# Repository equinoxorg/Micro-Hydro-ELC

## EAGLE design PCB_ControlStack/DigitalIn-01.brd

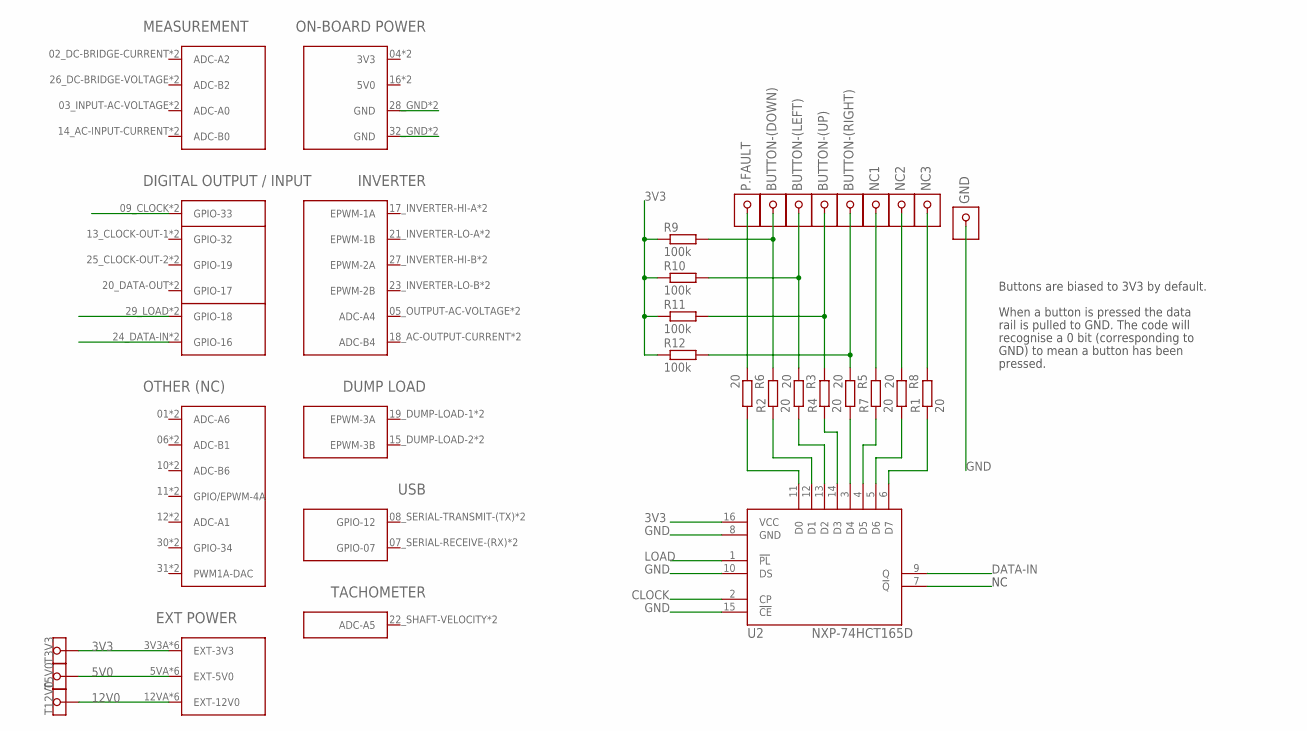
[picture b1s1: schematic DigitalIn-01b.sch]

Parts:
BUTTON-(DOWN): 1X1HEADER(W/VIA)
BUTTON-(LEFT): 1X1HEADER(W/VIA)
BUTTON-(RIGHT): 1X1HEADER(W/VIA)
BUTTON-(UP): 1X1HEADER(W/VIA)
GND: 1X1HEADER(W/VIA)
NC1, NC2, NC3: 1X1HEADER(W/VIA)
P.FAULT: 1X1HEADER(W/VIA)
R1, R2, R3, R4, R5, R6, R7, R8: 20; R0805
R9, R10, R11, R12: 100k; R0805
T3V3, T5V0, T12V0: TESTPAD
U1: CONTROLLER_STACK
U2: NXP-74HCT165D; SOIC-16D

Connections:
3V3: R9.1, R10.1, R11.1, R12.1, T3V3.TP, U1.3V3A (EXT-3V3), U1.3V3B (EXT-3V3), U1.3V3C (EXT-3V3), U1.3V3D (EXT-3V3), U1.3V3E (EXT-3V3), U1.3V3F (EXT-3V3), U2.16 (VCC)
5V0: T5V0.TP, U1.5VA (EXT-5V0), U1.5VB (EXT-5V0), U1.5VC (EXT-5V0), U1.5VD (EXT-5V0), U1.5VE (EXT-5V0), U1.5VF (EXT-5V0)
12V0: T12V0.TP, U1.12VA (EXT-12V0), U1.12VB (EXT-12V0), U1.12VC (EXT-12V0), U1.12VD (EXT-12V0), U1.12VE (EXT-12V0), U1.12VF (EXT-12V0)
CLOCK: U1.09_CLOCK (GPIO-33), U1.C9 (GPIO-33), U2.2 (CP)
DATA-IN: U1.24_DATA-IN (GPIO-16), U1.C24 (GPIO-16), U2.9 (Q)
GND: GND.P$2, GND.P$3, GND.P$4, GND.PAD, U1.28_GND (GND), U1.32_GND (GND), U1.C28 (GND), U1.C32 (GND), U2.8 (GND), U2.10 (DS), U2.15 (!CE)
LOAD: U1.29_LOAD (GPIO-18), U1.C29 (GPIO-18), U2.1 (!PL)
unnamed: R6.2, U2.11 (D0)
unnamed: R2.1, U2.12 (D1)
unnamed: R3.2, U2.13 (D2)
unnamed: R4.1, U2.14 (D3)
unnamed: P.FAULT.P$2, P.FAULT.P$3, P.FAULT.P$4, P.FAULT.PAD, R6.1
unnamed: R7.1, U2.4 (D5)
unnamed: R8.2, U2.5 (D6)
unnamed: R1.1, U2.6 (D7)
unnamed: R5.2, U2.3 (D4)
unnamed: BUTTON-(DOWN).P$2, BUTTON-(DOWN).P$3, BUTTON-(DOWN).P$4, BUTTON-(DOWN).PAD, R2.2, R9.2
unnamed: BUTTON-(LEFT).P$2, BUTTON-(LEFT).P$3, BUTTON-(LEFT).P$4, BUTTON-(LEFT).PAD, R3.1, R10.2
unnamed: BUTTON-(UP).P$2, BUTTON-(UP).P$3, BUTTON-(UP).P$4, BUTTON-(UP).PAD, R4.2, R11.2
unnamed: BUTTON-(RIGHT).P$2, BUTTON-(RIGHT).P$3, BUTTON-(RIGHT).P$4, BUTTON-(RIGHT).PAD, R5.1, R12.2
unnamed: NC1.P$2, NC1.P$3, NC1.P$4, NC1.PAD, R7.2
unnamed: NC2.P$2, NC2.P$3, NC2.P$4, NC2.PAD, R8.1
unnamed: NC3.P$2, NC3.P$3, NC3.P$4, NC3.PAD, R1.2

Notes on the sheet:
Buttons are biased to 3V3 by default.
When a button is pressed the data
rail is pulled to GND. The code will
recognise a 0 bit (corresponding to
GND) to mean a button has been
pressed.

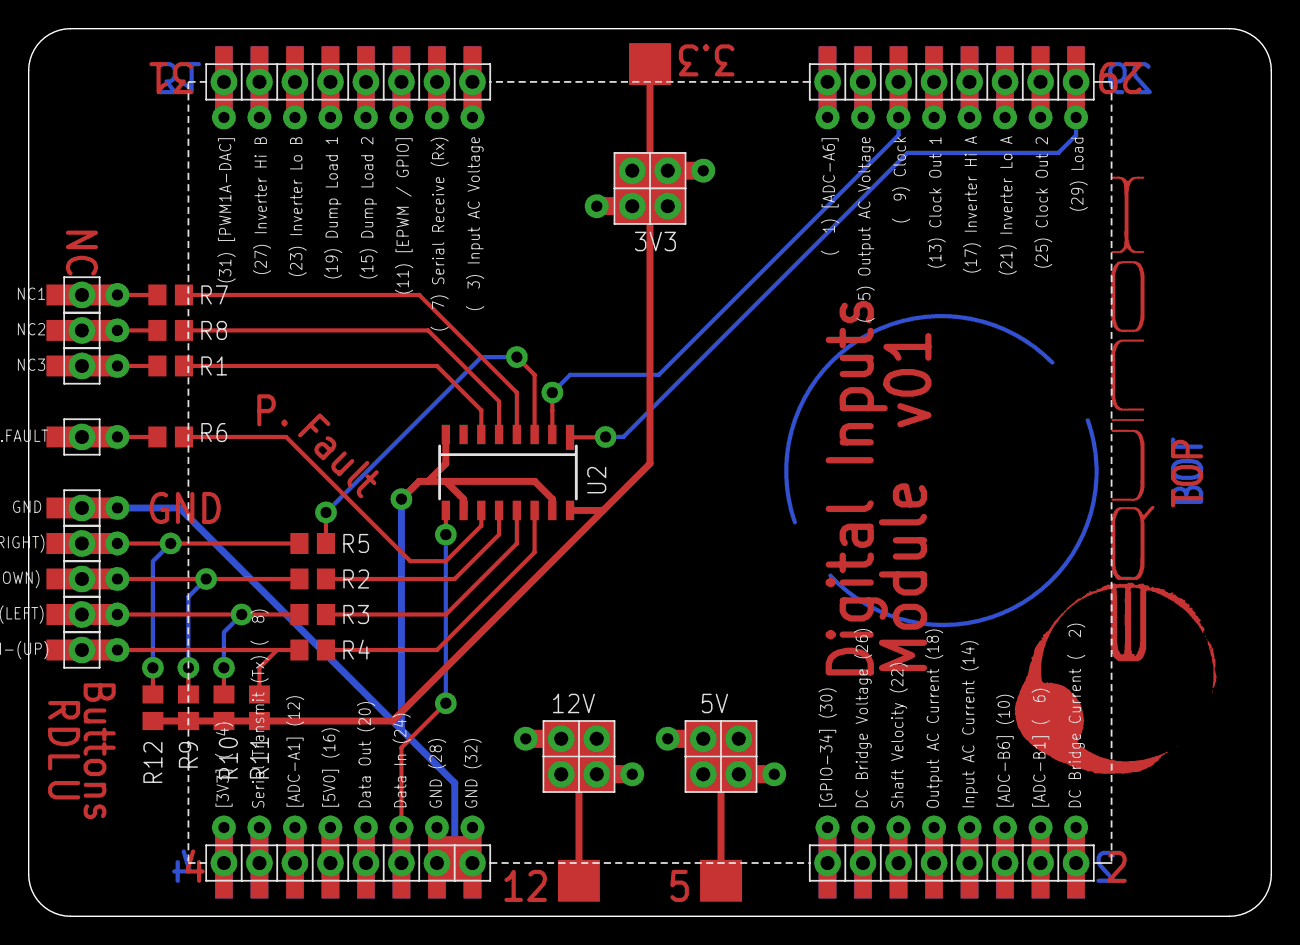
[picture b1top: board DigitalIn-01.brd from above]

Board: 2 copper layers, 88.9 x 63.5 mm, 26 parts (0 on the bottom side), 23 nets.

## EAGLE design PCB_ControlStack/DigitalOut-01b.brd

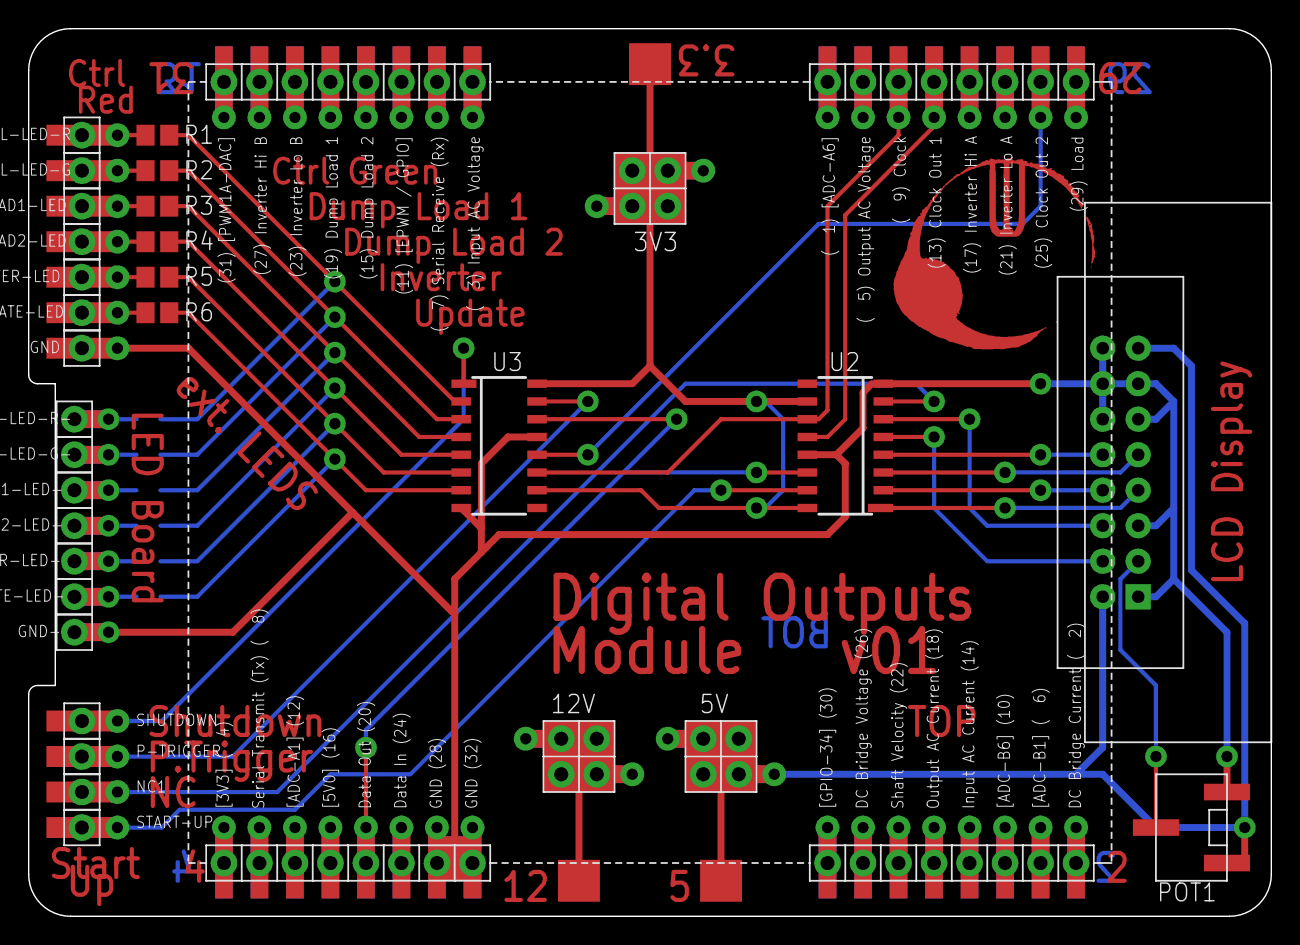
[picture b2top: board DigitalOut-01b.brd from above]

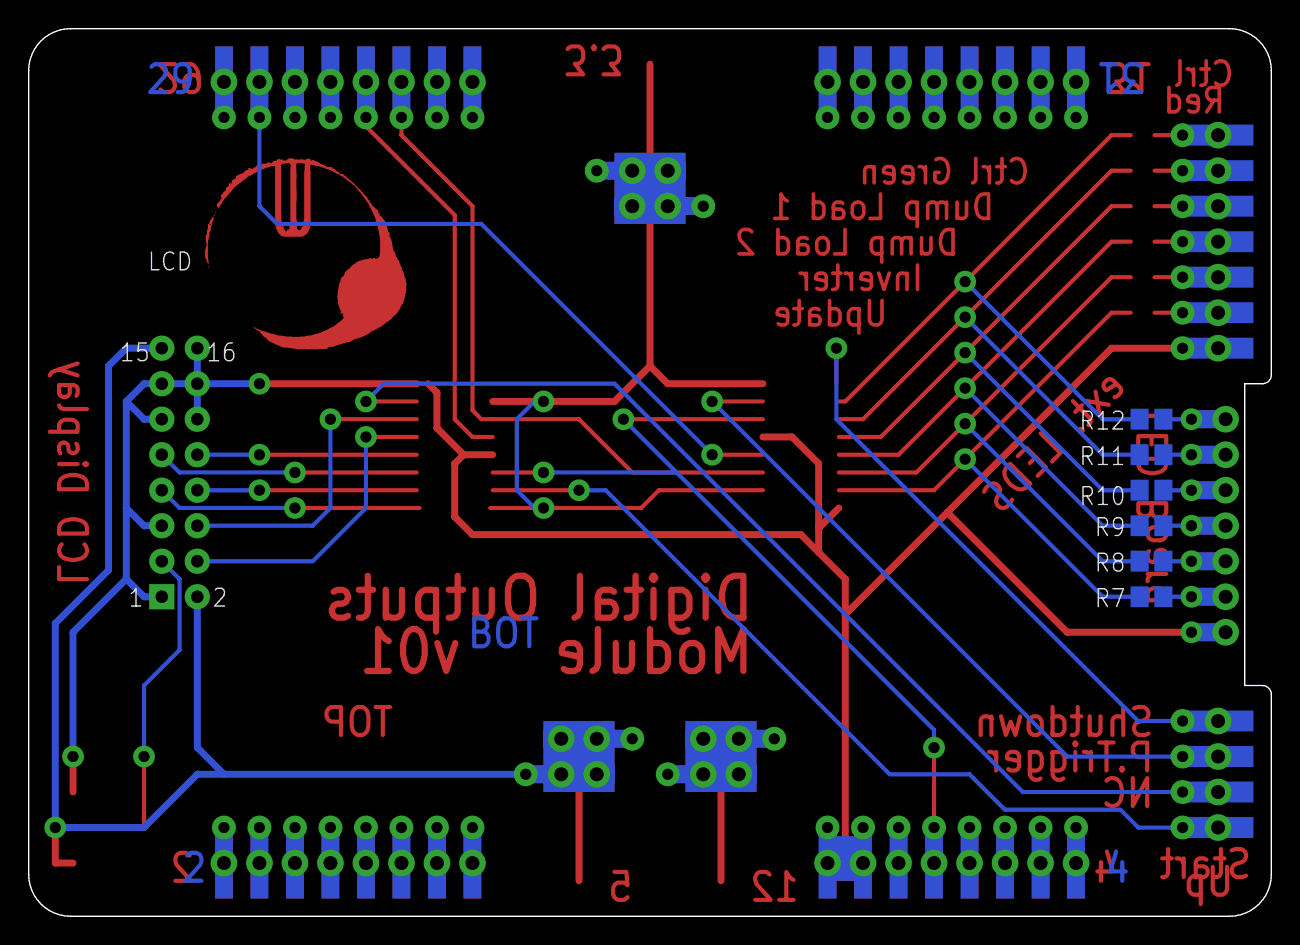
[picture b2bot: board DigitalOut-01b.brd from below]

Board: 2 copper layers, 88.9 x 63.5 mm, 38 parts (6 on the bottom side), 37 nets.

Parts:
CTRL-LED-G: 1X1HEADER(W/VIA)
CTRL-LED-G-: 1X1HEADER
CTRL-LED-R: 1X1HEADER(W/VIA)
CTRL-LED-R-: 1X1HEADER
DUMPLOAD1-LED, DUMPLOAD2-LED: 1X1HEADER(W/VIA)
DUMPLOAD1-LED-, DUMPLOAD2-LED-: 1X1HEADER
GND: 1X1HEADER(W/VIA)
GND-: 1X1HEADER
INVERTER-LED: 1X1HEADER(W/VIA)
INVERTER-LED-: 1X1HEADER
NC1: 1X1HEADER(W/VIA)
P-TRIGGER: 1X1HEADER(W/VIA)
POT1: BOURNS-3361S
R1, R2, R3, R4, R5, R6, R7, R8, R9, R10, R11, R12: 150; R0805
SHUTDOWN: 1X1HEADER(W/VIA)
START-UP: 1X1HEADER(W/VIA)
T3V3, T5V0, T12V0: TESTPAD
U1: CONTROLLER_STACK
U2, U3: TI-SN74AHC595D; SOIC-16D
U4: MULTICOMP-MC9B232
UPDATE-LED: 1X1HEADER(W/VIA)
UPDATE-LED-: 1X1HEADER

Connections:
3V3: T3V3.TP, U1.3V3A, U1.3V3B, U1.3V3C, U1.3V3D, U1.3V3E, U1.3V3F, U2.10, U2.16, U3.10, U3.16
5V0: POT1.2, T5V0.TP, U1.5VA, U1.5VB, U1.5VC, U1.5VD, U1.5VE, U1.5VF, U4.2, U4.15
12V0: T12V0.TP, U1.12VA, U1.12VB, U1.12VC, U1.12VD, U1.12VE, U1.12VF
CLOCK: U1.09_CLOCK, U1.C9, U2.11, U3.11
CLOCK-OUT-1: U1.13_CLOCK-OUT-1, U1.C13, U2.12
CLOCK-OUT-2: U1.25_CLOCK-OUT-2, U1.C25, U3.12
CONTRAST: POT1.3, U4.3
CTRL-LED-1: R1.1, R12.1, U3.2
CTRL-LED-2: R2.2, R11.2, U3.3
DATA-OUT: U1.20_DATA-OUT, U1.C20, U2.14, U3.14
DB0: U2.1, U4.7
DB1: U2.2, U4.8
DB2: U2.3, U4.9
DB3: U2.4, U4.10
DUMPLOAD1-LED: R3.1, R10.1, U3.4
DUMPLOAD2-LED: R4.2, R9.2, U3.5
ENABLE: U2.6, U4.6
GND: GND.P$2, GND.P$3, GND.P$4, GND.PAD, GND-.P$1, POT1.1, U1.28_GND, U1.32_GND, U1.C28, U1.C32, U2.8, U2.13, U3.8, U3.13, U4.1, U4.5, U4.11, U4.12, U4.13, U4.14, U4.16
INVERTER-LED: R5.1, R8.1, U3.6
unnamed: R7.1, UPDATE-LED-.P$1
unnamed: INVERTER-LED-.P$1, R8.2
unnamed: DUMPLOAD2-LED-.P$1, R9.1
unnamed: DUMPLOAD1-LED-.P$1, R10.2
unnamed: CTRL-LED-G-.P$1, R11.1
unnamed: CTRL-LED-R.P$2, CTRL-LED-R.P$3, CTRL-LED-R.P$4, CTRL-LED-R.PAD, R1.2
unnamed: CTRL-LED-R-.P$1, R12.2
unnamed: CTRL-LED-G.P$2, CTRL-LED-G.P$3, CTRL-LED-G.P$4, CTRL-LED-G.PAD, R2.1
unnamed: DUMPLOAD1-LED.P$2, DUMPLOAD1-LED.P$3, DUMPLOAD1-LED.P$4, DUMPLOAD1-LED.PAD, R3.2
unnamed: DUMPLOAD2-LED.P$2, DUMPLOAD2-LED.P$3, DUMPLOAD2-LED.P$4, DUMPLOAD2-LED.PAD, R4.1
unnamed: NC1.P$2, NC1.P$3, NC1.P$4, NC1.PAD, U2.7
unnamed: INVERTER-LED.P$2, INVERTER-LED.P$3, INVERTER-LED.P$4, INVERTER-LED.PAD, R5.2
unnamed: R6.1, UPDATE-LED.P$2, UPDATE-LED.P$3, UPDATE-LED.P$4, UPDATE-LED.PAD
P-TRIGGER: P-TRIGGER.P$2, P-TRIGGER.P$3, P-TRIGGER.P$4, P-TRIGGER.PAD, U3.15
RS: U2.5, U4.4
SHUTDOWN: SHUTDOWN.P$2, SHUTDOWN.P$3, SHUTDOWN.P$4, SHUTDOWN.PAD, U3.1
START-UP: START-UP.P$2, START-UP.P$3, START-UP.P$4, START-UP.PAD, U2.15
UPDATE-LED: R6.2, R7.2, U3.7

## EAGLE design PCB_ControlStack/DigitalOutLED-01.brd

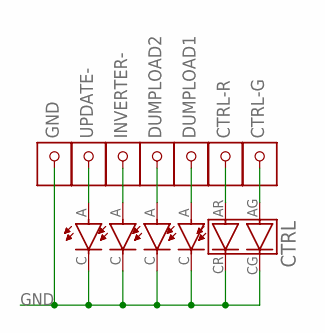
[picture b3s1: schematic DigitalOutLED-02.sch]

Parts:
CTRL: PLCC4-RG; PLCC4
CTRL-G: 1X1HEADER
CTRL-R: 1X1HEADER
DL1, DL2: PLCC2
DUMPLOAD1, DUMPLOAD2: 1X1HEADER
GND: 1X1HEADER
INVERTER: PLCC2
INVERTER-: 1X1HEADER
UPDATE: PLCC2
UPDATE-: 1X1HEADER

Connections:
GND: CTRL.CG, CTRL.CR, DL1.C, DL2.C, GND.P$1, INVERTER.C, UPDATE.C
unnamed: UPDATE.A, UPDATE-.P$1
unnamed: INVERTER.A, INVERTER-.P$1
unnamed: DL2.A, DUMPLOAD2.P$1
unnamed: DL1.A, DUMPLOAD1.P$1
unnamed: CTRL.AR, CTRL-R.P$1
unnamed: CTRL.AG, CTRL-G.P$1

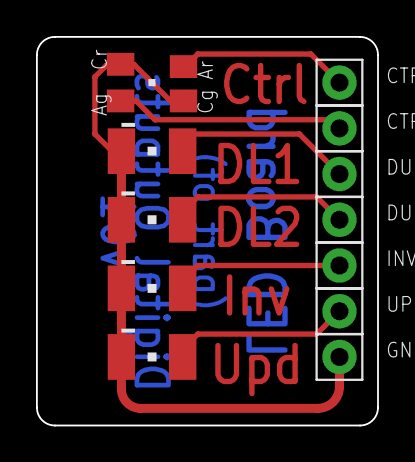
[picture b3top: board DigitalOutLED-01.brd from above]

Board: 2 copper layers, 18.9 x 21.6 mm, 12 parts (0 on the bottom side), 7 nets.

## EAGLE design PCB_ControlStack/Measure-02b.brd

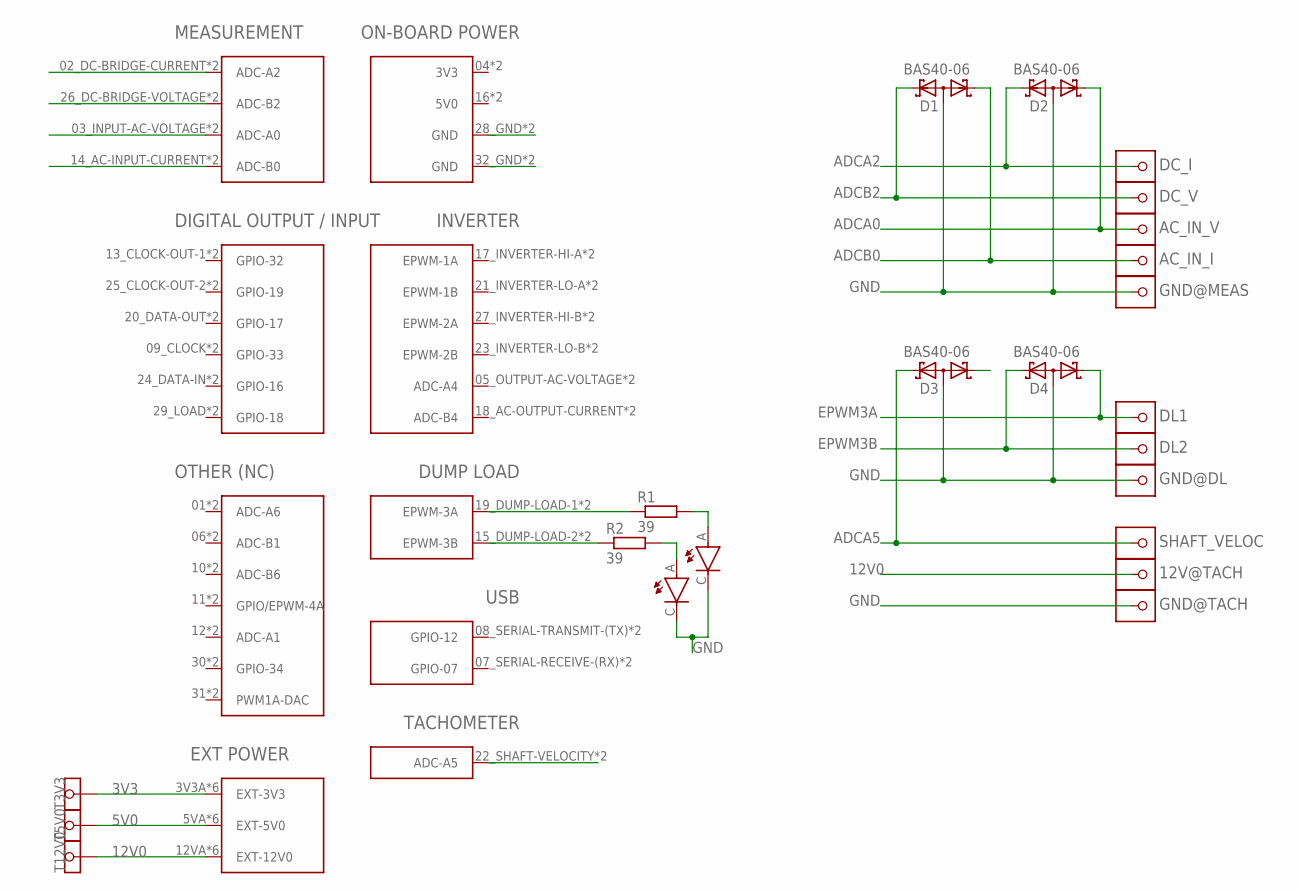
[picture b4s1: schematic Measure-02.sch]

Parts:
12V@TACH: 1X1HEADER(W/VIA)
AC_IN_I: 1X1HEADER(W/VIA)
AC_IN_V: 1X1HEADER(W/VIA)
D1, D2, D3, D4: BAS40-06; SOT23
DC_I: 1X1HEADER(W/VIA)
DC_V: 1X1HEADER(W/VIA)
DL1, DL2: 1X1HEADER(W/VIA)
DL.1, DL.2: PLCC2
GND@DL: 1X1HEADER(W/VIA)
GND@MEAS: 1X1HEADER(W/VIA)
GND@TACH: 1X1HEADER(W/VIA)
R1, R2: 39; R0805
SHAFT_VELOC: 1X1HEADER(W/VIA)
T3V3, T5V0, T12V0: TESTPAD
U$1: CONTROLLER_STACK

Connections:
3V3: T3V3.TP, U$1.3V3A (EXT-3V3), U$1.3V3B (EXT-3V3), U$1.3V3C (EXT-3V3), U$1.3V3D (EXT-3V3), U$1.3V3E (EXT-3V3), U$1.3V3F (EXT-3V3)
5V0: T5V0.TP, U$1.5VA (EXT-5V0), U$1.5VB (EXT-5V0), U$1.5VC (EXT-5V0), U$1.5VD (EXT-5V0), U$1.5VE (EXT-5V0), U$1.5VF (EXT-5V0)
12V0: 12V@TACH.P$2, 12V@TACH.P$3, 12V@TACH.P$4, 12V@TACH.PAD, T12V0.TP, U$1.12VA (EXT-12V0), U$1.12VB (EXT-12V0), U$1.12VC (EXT-12V0), U$1.12VD (EXT-12V0), U$1.12VE (EXT-12V0), U$1.12VF (EXT-12V0)
ADCA0: AC_IN_V.P$2, AC_IN_V.P$3, AC_IN_V.P$4, AC_IN_V.PAD, D2.1 (K1), U$1.03_INPUT-AC-VOLTAGE (ADC-A0), U$1.C3 (ADC-A0)
ADCA2: D2.2 (K2), DC_I.P$2, DC_I.P$3, DC_I.P$4, DC_I.PAD, U$1.02_DC-BRIDGE-CURRENT (ADC-A2), U$1.C2 (ADC-A2)
ADCA5: D3.2 (K2), SHAFT_VELOC.P$2, SHAFT_VELOC.P$3, SHAFT_VELOC.P$4, SHAFT_VELOC.PAD, U$1.22_SHAFT-VELOCITY (ADC-A5), U$1.C22 (ADC-A5)
ADCB0: AC_IN_I.P$2, AC_IN_I.P$3, AC_IN_I.P$4, AC_IN_I.PAD, D1.1 (K1), U$1.14_AC-INPUT-CURRENT (ADC-B0), U$1.C14 (ADC-B0)
ADCB2: D1.2 (K2), DC_V.P$2, DC_V.P$3, DC_V.P$4, DC_V.PAD, U$1.26_DC-BRIDGE-VOLTAGE (ADC-B2), U$1.C26 (ADC-B2)
EPWM3A: D4.1 (K1), DL1.P$2, DL1.P$3, DL1.P$4, DL1.PAD, R1.1, U$1.19_DUMP-LOAD-1 (EPWM-3A), U$1.C19 (EPWM-3A)
EPWM3B: D4.2 (K2), DL2.P$2, DL2.P$3, DL2.P$4, DL2.PAD, R2.1, U$1.15_DUMP-LOAD-2 (EPWM-3B), U$1.C15 (EPWM-3B)
GND: D1.3 (AA), D2.3 (AA), D3.3 (AA), D4.3 (AA), DL.1.C, DL.2.C, GND@DL.P$2, GND@DL.P$3, GND@DL.P$4, GND@DL.PAD, GND@MEAS.P$2, GND@MEAS.P$3, GND@MEAS.P$4, GND@MEAS.PAD, GND@TACH.P$2, GND@TACH.P$3, GND@TACH.P$4, GND@TACH.PAD, U$1.28_GND (GND), U$1.32_GND (GND), U$1.C28 (GND), U$1.C32 (GND)
unnamed: DL.2.A, R2.2
unnamed: DL.1.A, R1.2
STARTUP: D3.1 (K1)

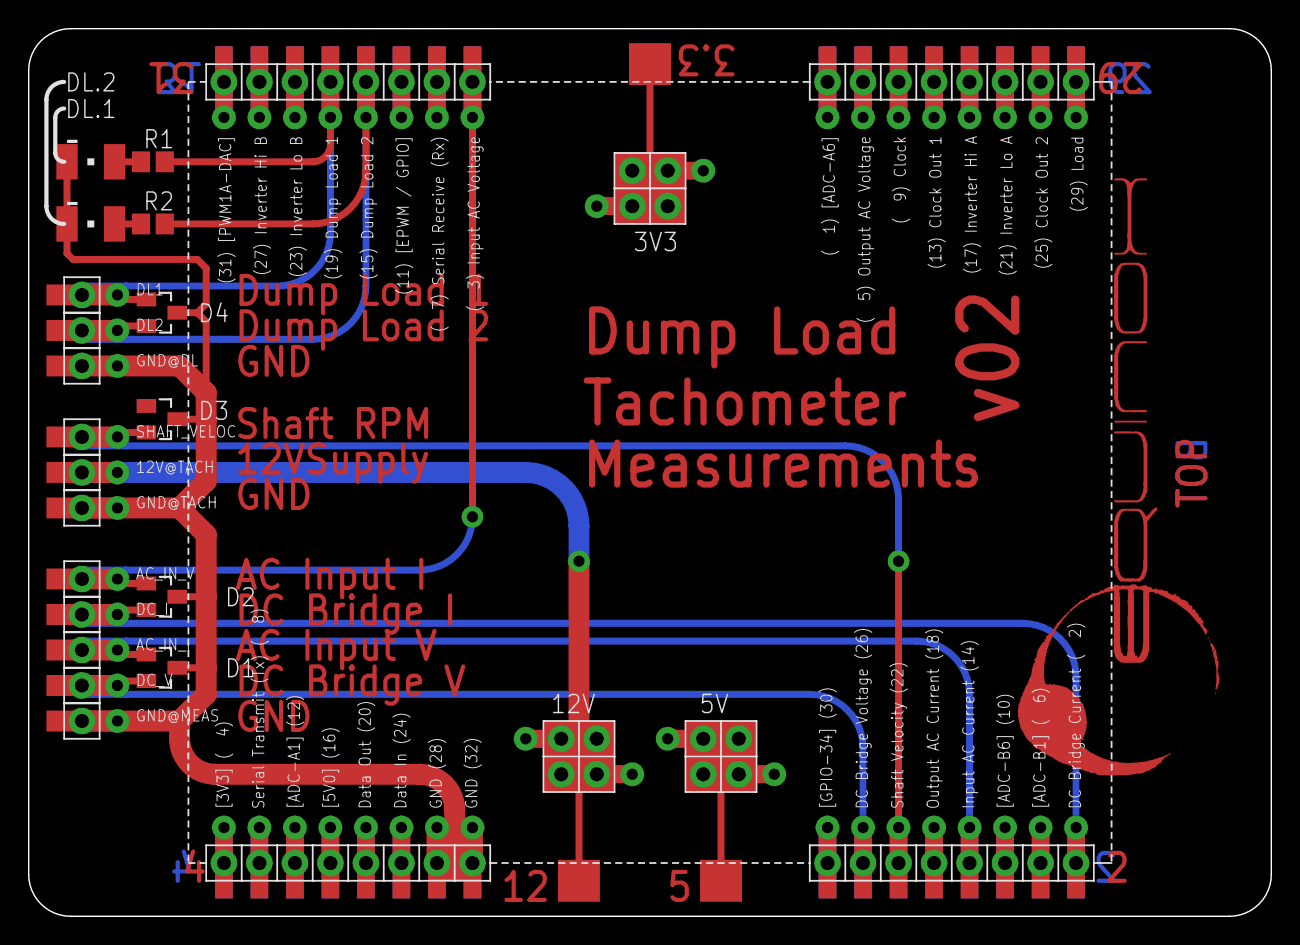
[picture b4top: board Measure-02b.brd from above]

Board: 2 copper layers, 88.9 x 63.5 mm, 23 parts (0 on the bottom side), 13 nets.

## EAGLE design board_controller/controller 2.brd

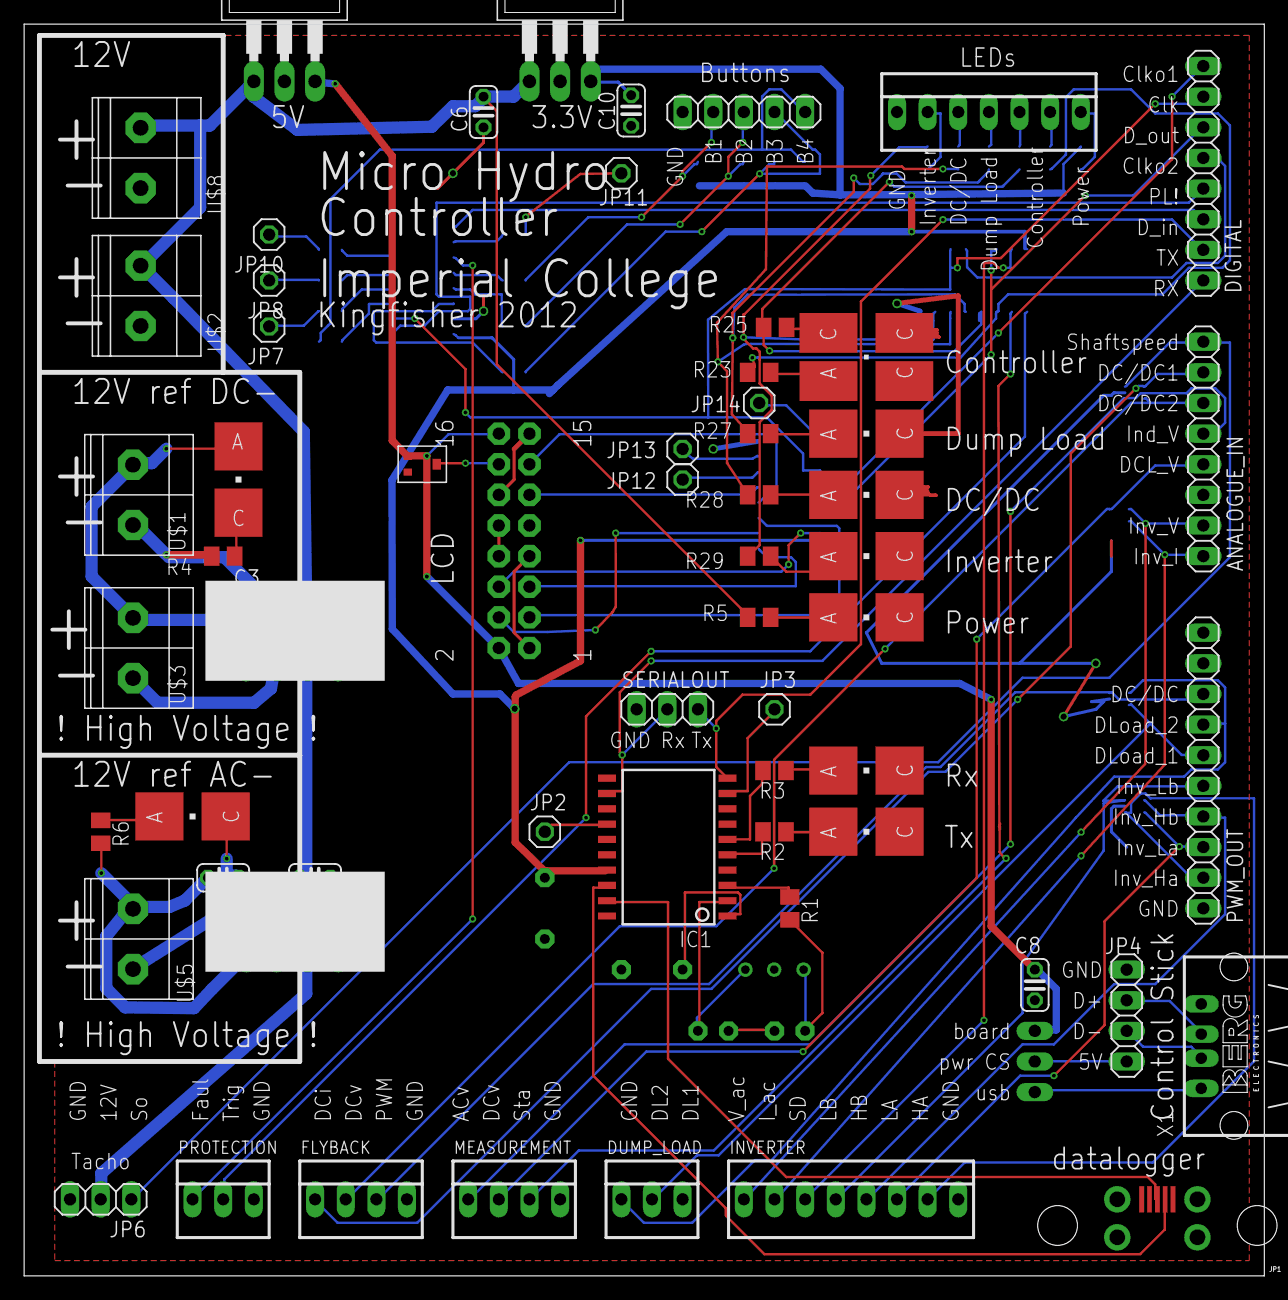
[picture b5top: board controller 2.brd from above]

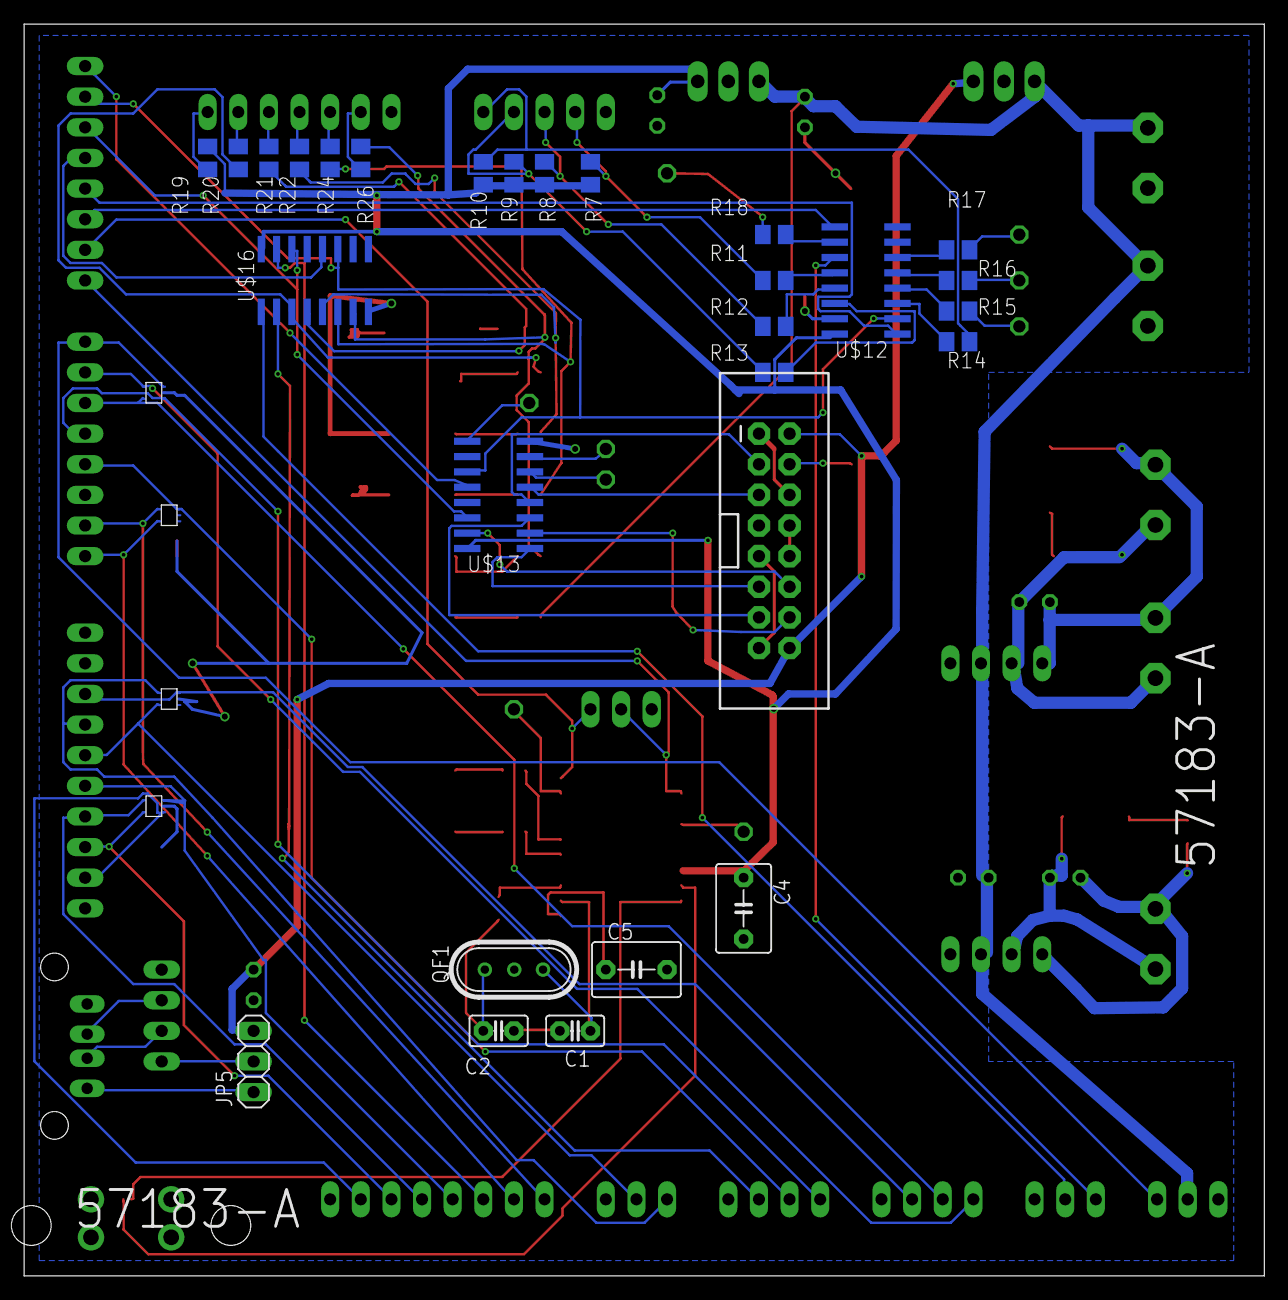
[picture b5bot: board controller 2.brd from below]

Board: 2 copper layers, 102.8 x 103.8 mm, 93 parts (32 on the bottom side), 95 nets.

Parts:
ANALOGUE_IN: 1X08
C1, C2: 39p; C2.5-2
C3, C9: 10u; C025-024X044
C4, C5: 0.1u; C5B4.5
C6: 20u; C025-024X044
C7: 0.33u; C025-024X044
C8, C10: 0.1u; C025-024X044
CONTR_GREEN: P-LCC-4
DC/DC: P-LCC-2
DC/DC_ON1, DC/DC_ON2, DC/DC_ON3, DC/DC_ON4: P-LCC-2
DIGITAL: 1X08
DUMP_LOAD: 22-23-2031
DUMP_LOAD_: P-LCC-2
FLYBACK: 22-23-2041
IC1: MCP2200SOIC20; SOIC20
INVERTER: 22-23-2081
INVERTER_: P-LCC-2
JP1: USB_MICROB_PLUG-SMT; MICRO-B-SMT
JP2, JP3, JP7, JP8, JP10, JP11, JP12, JP13, JP14: 1X01
JP4: 1X04
JP5, JP6: 1X03
JP9: 1X05
LCD_SCREEN: M08X2-SHROUDED_LOCK; 2X8-SHROUDED_LOCK
LED1: P-LCC-2
MEASUREMENT: 22-23-2041
PROTECTION: 22-23-2031
PWM_OUT: 1X10
QF1: 10M7AHC49T; HC49U
R1: 0; M0805
R2, R3, R19, R20, R21, R22, R23, R24, R25, R26, R27, R28, R29: 200; M0805
R4, R5, R6: 1.2k; M0805
R7, R8, R9, R10: 100k; M0805
R11, R12, R13, R14, R15, R16, R17, R18: 20; M0805
SERIALOUT: 1X03
U$1, U$2, U$3, U$5, U$8: CTB1500/2; CTB1500-2
U$4, U$6: KFP_DC-DC12V; KFP_DC-DC
U$7, U$9: KFP_VOLTAGE_REGULATOR; TO220
U$10, U$11, U$14, U$15: EVS_NXP
U$12: 74HC165; SO16
U$13, U$16: SN74AHC594; SO16
U$17: 10k; MURATA_PVZ2A
X1: PN87520
X2: 22-23-2071

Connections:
3.3V: C4.1, C10.2, IC1.17, R7.1, R8.1, R9.1, R10.1, R19.1, U$9.3, U$12.16, U$13.16, U$16.16
5V: C8.1, JP5.3, LCD_SCREEN.2, LCD_SCREEN.16, U$7.3, U$17.1
12V: C6.2, C7.2, JP6.2, R5.1, U$2.P$2, U$4.+VIN, U$6.+VIN, U$7.1, U$8.P$2, U$9.1
CLOCK: DIGITAL.2, U$12.2, U$13.11, U$16.11
CTR_PICCOLO_POWER: JP4.1, JP5.2
D1: LCD_SCREEN.12, U$13.15
D2: LCD_SCREEN.11, U$13.1
D3: LCD_SCREEN.14, U$13.2
D4: LCD_SCREEN.13, U$13.3
DATA_IN: DIGITAL.6, U$12.9
DC/DC_IN_1: ANALOGUE_IN.6, FLYBACK.2, U$15.P$5
DC/DC_IN_2: ANALOGUE_IN.7, FLYBACK.1, U$15.P$4
DC/DC_ON: R26.1, R29.2, U$16.7
DUMP_LOAD1: DUMP_LOAD.2, PWM_OUT.6, U$11.P$5
DUMP_LOAD2: DUMP_LOAD.1, PWM_OUT.7, U$11.P$4
DUMP_LOAD_1_ON: R22.1, R27.2, U$16.5
E: LCD_SCREEN.5, U$13.5
FLYBACK: FLYBACK.3, PWM_OUT.8, U$11.P$3
GND: C4.2, C5.2, C6.1, C7.1, C8.2, C10.1, CONTR_GREEN.C@4, DC/DC.C, DC/DC_ON2.C, DC/DC_ON3.C, DUMP_LOAD.3, DUMP_LOAD_.C, FLYBACK.4, IC1.20, INVERTER.8, INVERTER_.C, JP4.4, JP6.3, JP9.5, LCD_SCREEN.1, LCD_SCREEN.6, LCD_SCREEN.7, LCD_SCREEN.8, LCD_SCREEN.9, LCD_SCREEN.10, LCD_SCREEN.15, LED1.C, MEASUREMENT.4, PROTECTION.3, PWM_OUT.1, SERIALOUT.3, U$2.P$1, U$4.-VIN, U$6.-VIN, U$7.2, U$8.P$1, U$9.2, U$10.P$2, U$11.P$2, U$12.8, U$12.15, U$13.8, U$14.P$2, U$15.P$2, U$16.8, U$17.3, X1.4, X2.1
INVERTER_ON: R24.1, R28.2, U$16.6
INV_HA: INVERTER.7, PWM_OUT.2, U$10.P$1
INV_HB: INVERTER.5, PWM_OUT.4, U$10.P$4
INV_I: ANALOGUE_IN.1, INVERTER.2, U$14.P$5
INV_LA: INVERTER.6, PWM_OUT.3, U$10.P$5
INV_LB: INVERTER.4, PWM_OUT.5, U$10.P$3
INV_V: ANALOGUE_IN.2, INVERTER.1, U$14.P$4
LOAD: DIGITAL.5, U$12.1
MEAS_AC: ANALOGUE_IN.5, MEASUREMENT.1, U$15.P$1
MEAS_DC: ANALOGUE_IN.4, MEASUREMENT.2, U$14.P$3
unnamed: R12.1, U$12.13
unnamed: LED1.A, R5.2
unnamed: R19.2, X2.7
unnamed: R16.1, U$12.5
unnamed: DC/DC_ON1.C, R4.2
unnamed: R17.1, U$12.6
unnamed: JP12.1, U$13.6
unnamed: IC1.3, R1.1
unnamed: DIGITAL.1, U$13.12
unnamed: JP13.1, U$13.7
unnamed: R20.1, R23.2, U$16.3
unnamed: C2.2, QF1.3, R1.2
unnamed: DC/DC_ON4.A, R6.1
unnamed: JP14.1, U$13.9
unnamed: R21.1, R25.2, U$16.4
unnamed: DIGITAL.3, U$13.14, U$16.14
unnamed: JP9.1, R10.2, R14.2
unnamed: JP9.2, R9.2, R13.2
unnamed: C3.1, DC/DC_ON1.A, U$1.P$2, U$3.P$2, U$4.+VOUT
unnamed: C1.1, C2.1
unnamed: C1.2, IC1.2, QF1.1
unnamed: C3.2, R4.1, U$1.P$1, U$3.P$1, U$4.-VOUT
unnamed: R20.2, X2.6
unnamed: R21.2, X2.5
unnamed: R22.2, X2.4
unnamed: JP9.3, R8.2, R12.2
unnamed: C9.2, R6.2, U$5.P$2, U$6.+VOUT
unnamed: C9.1, DC/DC_ON4.C, U$5.P$1, U$6.-VOUT
unnamed: DIGITAL.4, U$16.12
unnamed: DUMP_LOAD_.A, R27.1
unnamed: DC/DC.A, R28.1
unnamed: INVERTER_.A, R29.1
unnamed: CONTR_GREEN.A, R23.1
unnamed: JP9.4, R7.2, R11.2
unnamed: R24.2, X2.3
unnamed: R26.2, X2.2
unnamed: R18.1, U$12.10
unnamed: R11.1, U$12.12
unnamed: R13.1, U$12.14
unnamed: R14.1, U$12.3
unnamed: R15.1, U$12.4
unnamed: JP7.1, R15.2
unnamed: JP8.1, R16.2
unnamed: JP10.1, R17.2
unnamed: JP11.1, R18.2
unnamed: DC/DC_ON2.A, R2.1
unnamed: DC/DC_ON3.A, R3.1
unnamed: C5.1, IC1.1
unnamed: IC1.5, R2.2
unnamed: IC1.6, R3.2
unnamed: IC1.14, JP2.1
unnamed: IC1.9, JP3.1
PROTEC_FAULT: PROTECTION.1, U$12.11
PROTEC_TRIGGER: PROTECTION.2, U$16.1
RS: LCD_SCREEN.3, U$13.4
RX: DIGITAL.8, IC1.12, SERIALOUT.2
SHAFTSPEED_IN: ANALOGUE_IN.8, JP6.1, U$15.P$3
SHUT_DOWN: INVERTER.3, U$16.15
START_UP: MEASUREMENT.3, U$16.2
TX: DIGITAL.7, IC1.10, SERIALOUT.1
USB_D+: JP4.3, X1.3
USB_D-: JP4.2, X1.2
USB_UART_D+: IC1.19, JP1.3
USB_UART_D-: IC1.18, JP1.2
V0: LCD_SCREEN.4, U$17.2
V_USB: JP5.1, X1.1

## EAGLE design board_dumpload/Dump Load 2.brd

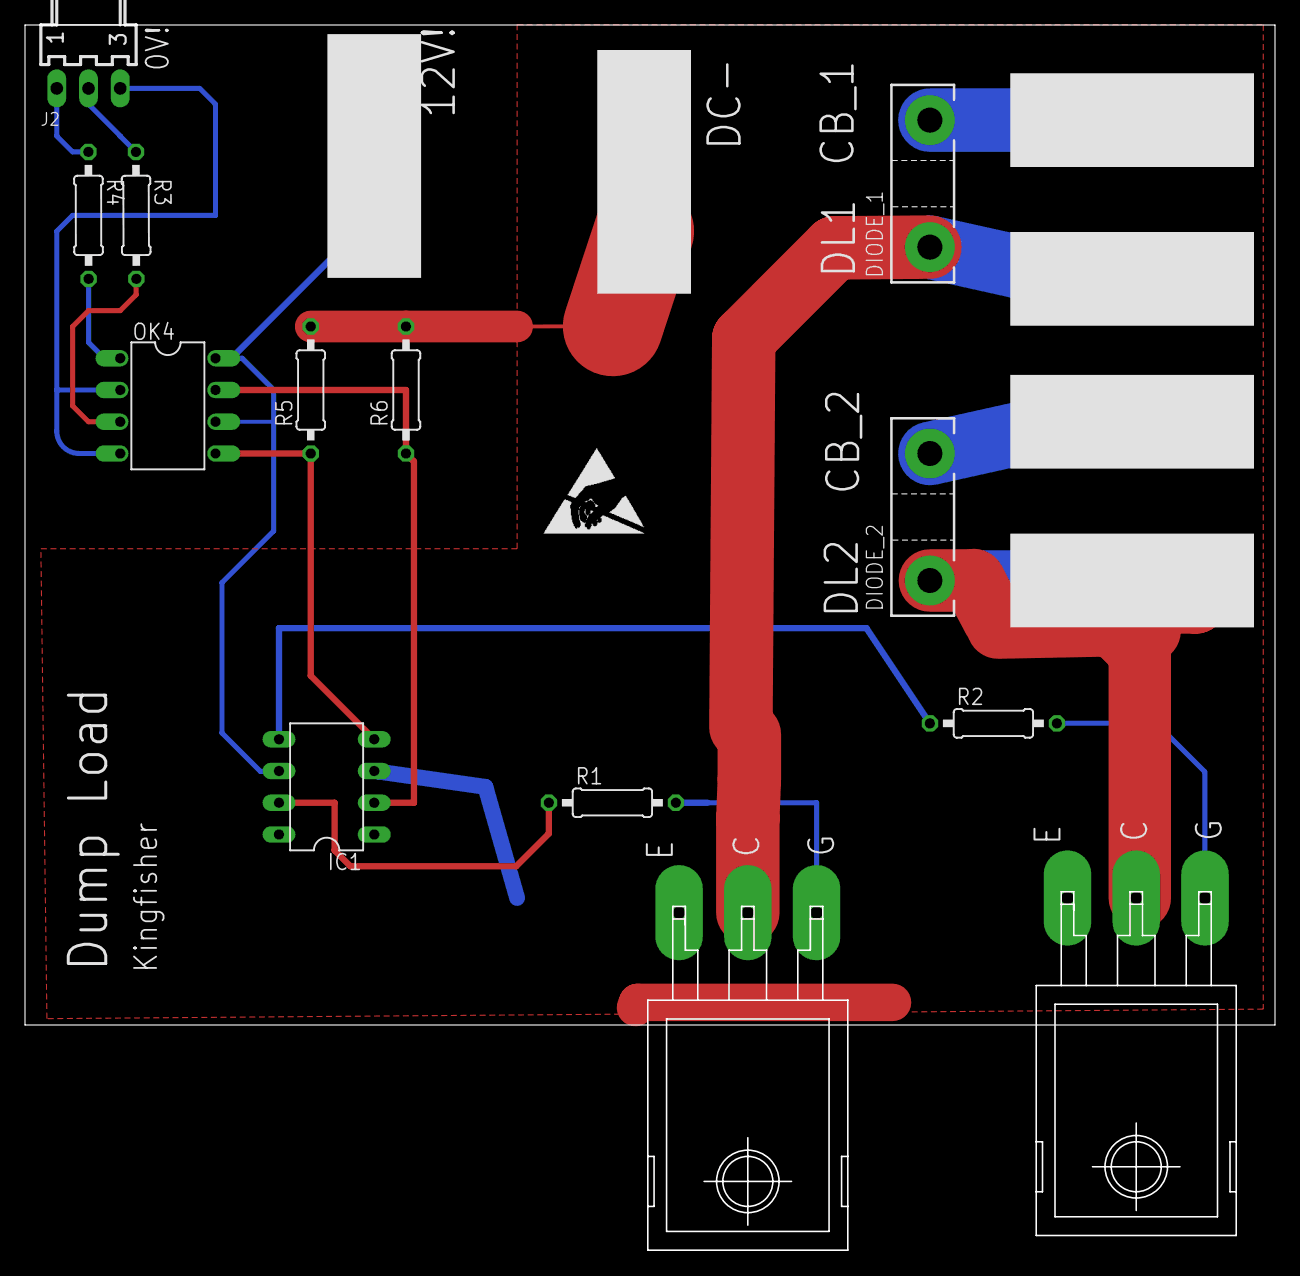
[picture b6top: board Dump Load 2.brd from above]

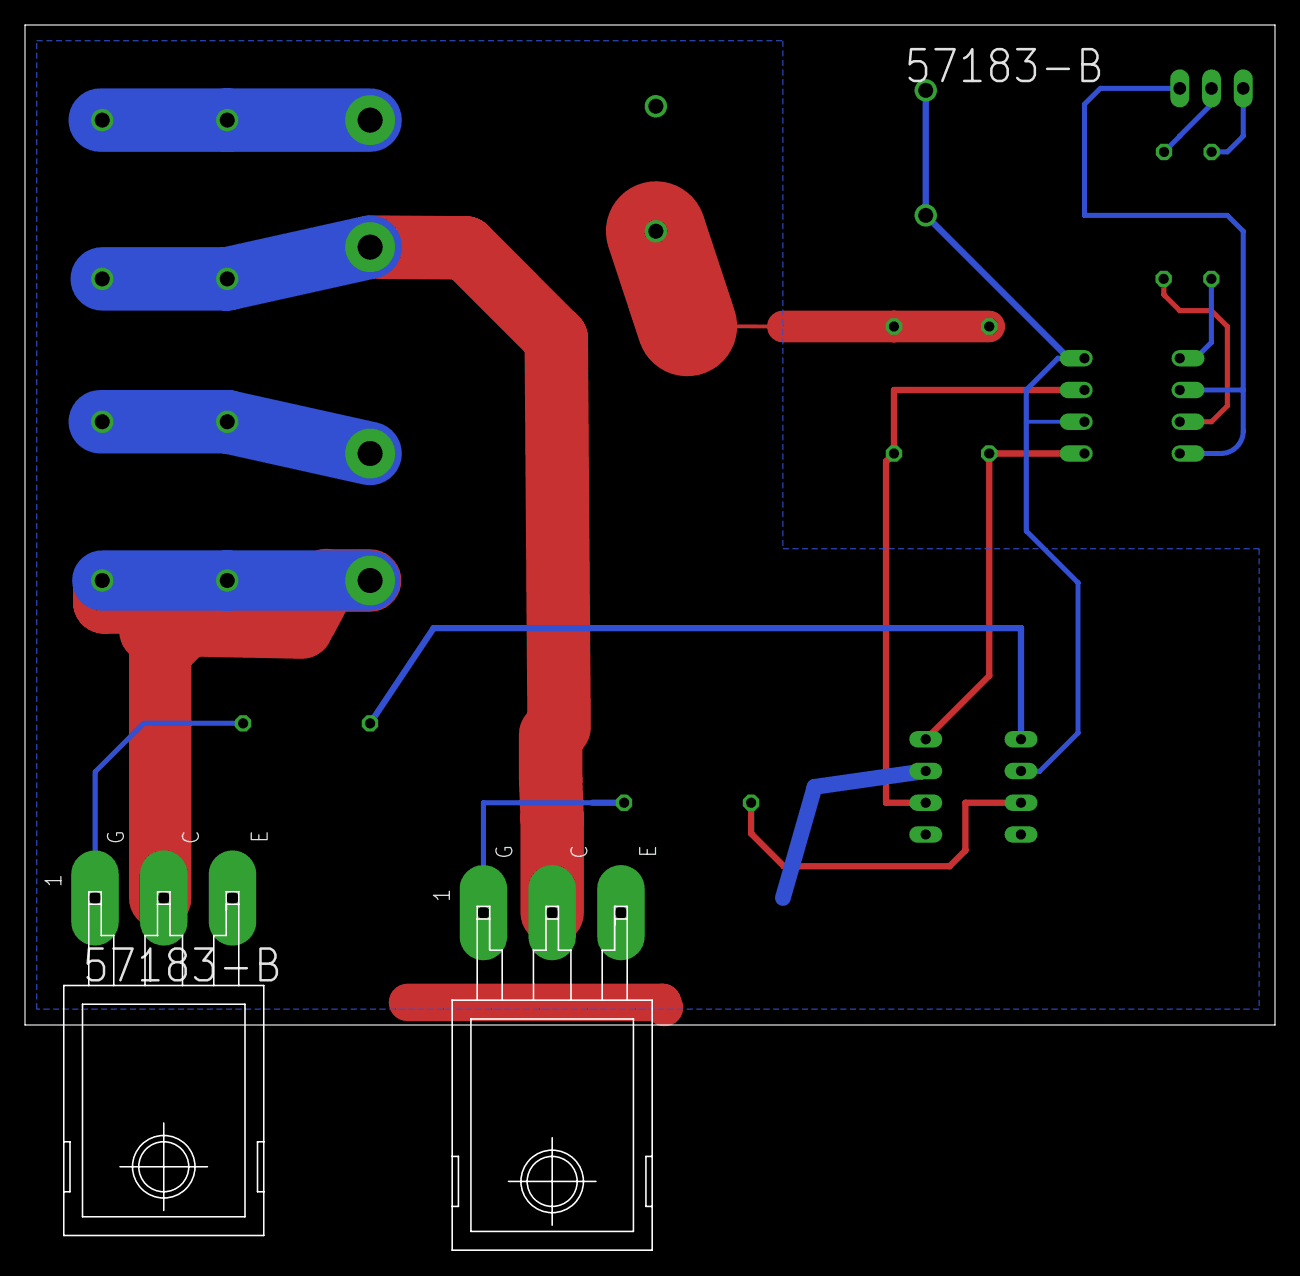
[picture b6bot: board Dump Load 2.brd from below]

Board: 2 copper layers, 100.0 x 80.0 mm, 19 parts (2 on the bottom side), 17 nets.

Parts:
DC_CB_1, DC_CB_2: HIGH_AMP_TERMINAL
DIODE_1, DIODE_2: TO-247-2V
DL1, DL2: HIGH_AMP_TERMINAL
IC1: DIL08
J2: 22-05-7038-03; 7395-03
OK4: TIL198; DIL08
R1, R2, R3, R4, R5, R6: 0207/10
U$1, U$2: TO-247C; TO-247-FLATUD
U$4: HIGH_AMP_TERMINAL
VCC_12V: HIGH_AMP_TERMINAL

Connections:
DC-: IC1.3, R5.2, R6.2, U$1.P$3, U$2.P$3, U$4.P$1, U$4.P$2
GND: J2.3, OK4.2, OK4.4
unnamed: R1.2, U$1.P$1
unnamed: R2.2, U$2.P$1
unnamed: IC1.4, OK4.5, R5.1
unnamed: IC1.7, R1.1
unnamed: IC1.5, R2.1
unnamed: J2.1, R4.1
unnamed: IC1.6, OK4.6, OK4.8, VCC_12V.P$1, VCC_12V.P$2
unnamed: DIODE_2.1, DL2.P$1, DL2.P$2, U$2.P$2
unnamed: OK4.3, R3.2
unnamed: J2.2, R3.1
unnamed: OK4.1, R4.2
unnamed: DC_CB_1.P$1, DC_CB_1.P$2, DIODE_1.2
unnamed: IC1.2, OK4.7, R6.1
unnamed: DIODE_1.1, DL1.P$1, DL1.P$2, U$1.P$2
unnamed: DC_CB_2.P$1, DC_CB_2.P$2, DIODE_2.2
